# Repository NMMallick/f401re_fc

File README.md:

# f401re_fc
Amateur prototype for a quad-copter flightcontroller on stm32f4 based chips

##

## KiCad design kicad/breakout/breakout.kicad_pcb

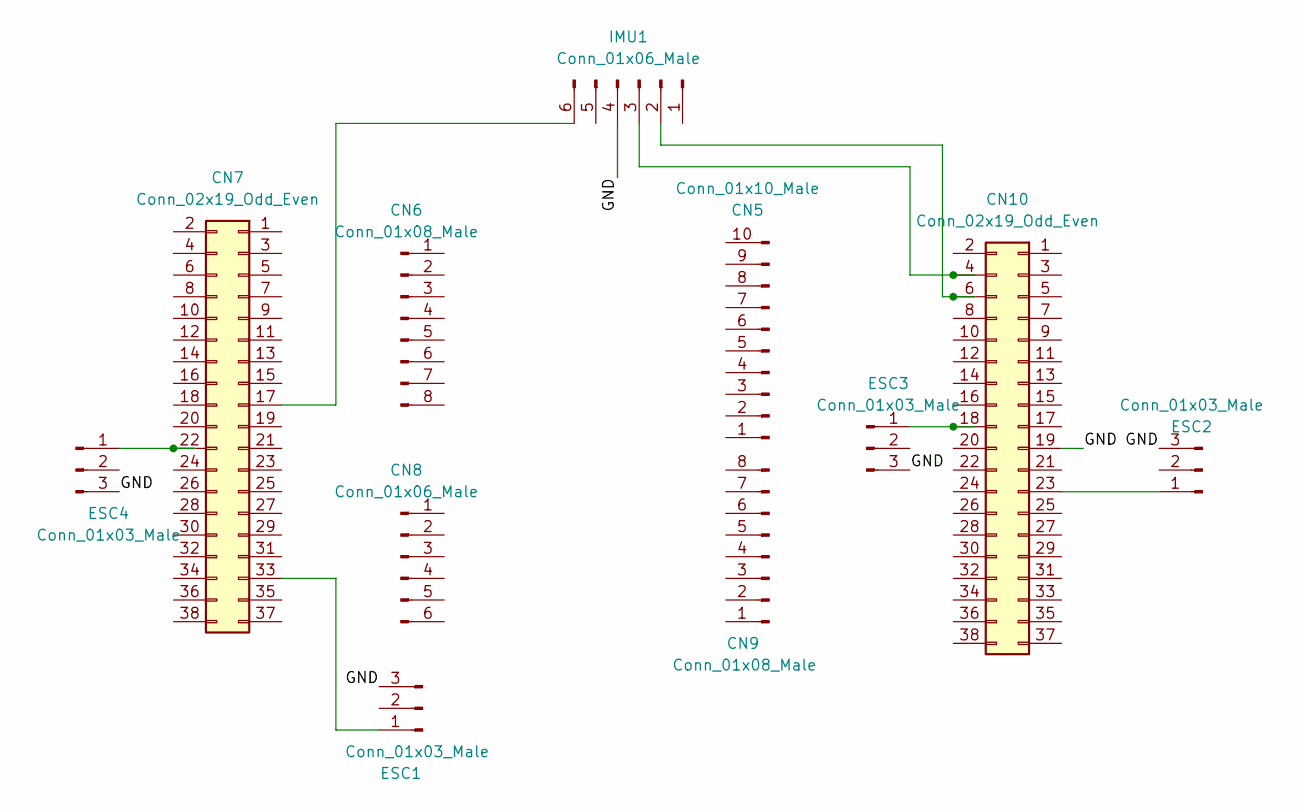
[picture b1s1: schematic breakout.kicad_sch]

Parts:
CN5: Conn_01x10_Male; PinHeader_1x10_P2.54mm_Vertical
CN6, CN9: Conn_01x08_Male; PinHeader_1x08_P2.54mm_Vertical
CN7, CN10: Conn_02x19_Odd_Even; PinSocket_2x19_P2.54mm_Vertical
CN8: Conn_01x06_Male; PinHeader_1x06_P2.54mm_Vertical
ESC1, ESC2, ESC3, ESC4: Conn_01x03_Male; PinHeader_1x03_P2.54mm_Vertical
IMU1: Conn_01x06_Male; PinHeader_1x06_P2.54mm_Vertical

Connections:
/GND: CN10.19, ESC1.3, ESC2.3, ESC3.3, ESC4.3, IMU1.4
unnamed: CN7.22, ESC4.1
unnamed: CN10.23, ESC2.1
unnamed: CN7.33, ESC1.1
unnamed: CN10.18, ESC3.1
unnamed: CN10.6, IMU1.2
unnamed: CN10.4, IMU1.3
unnamed: CN7.17, IMU1.6

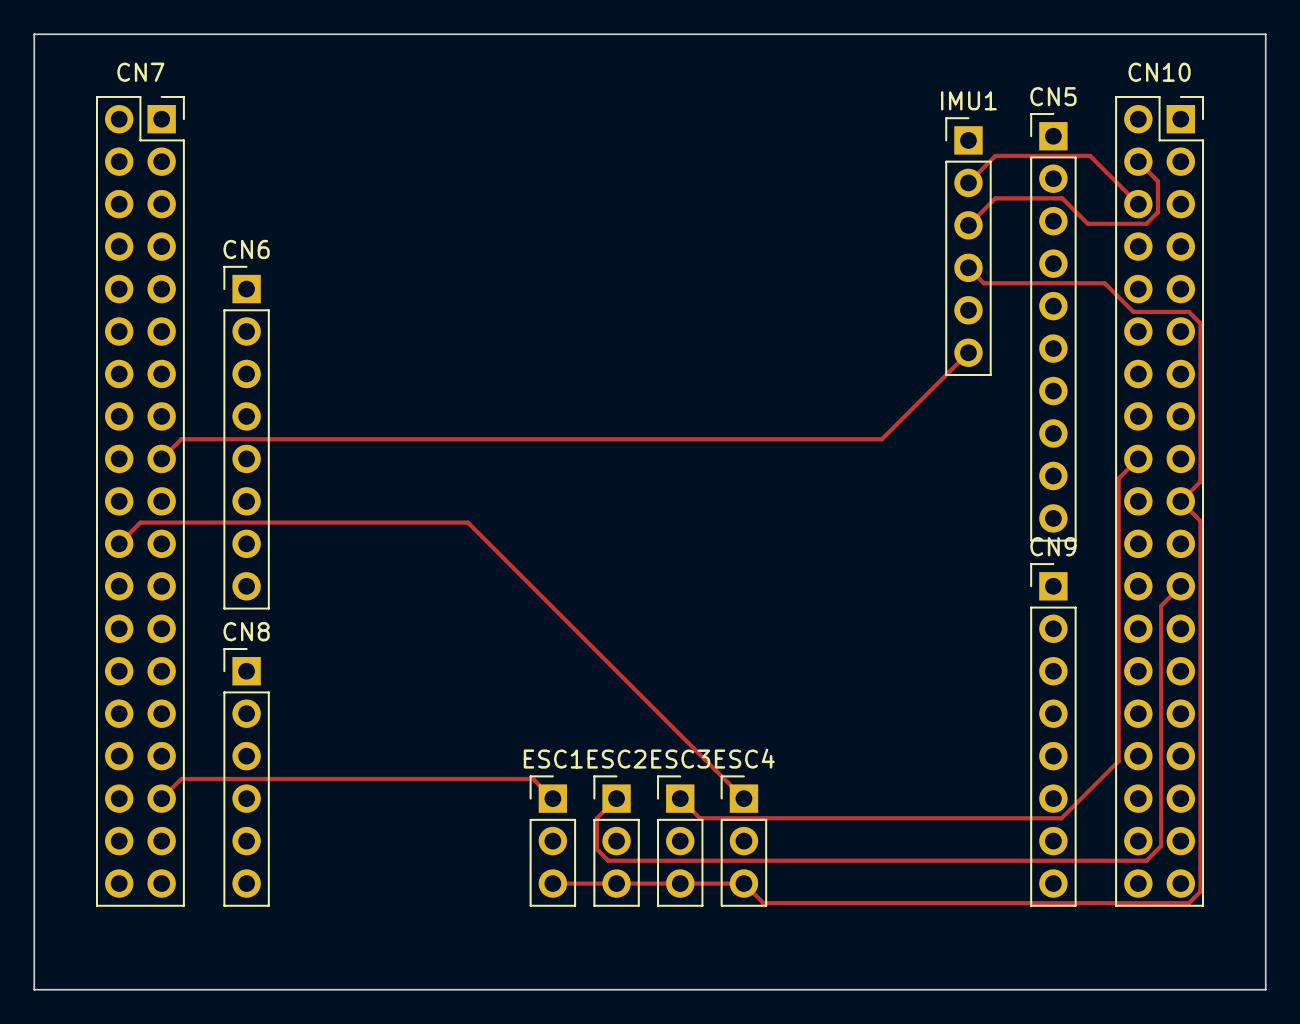
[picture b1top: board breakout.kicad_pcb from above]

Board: 2 copper layers, 73.7 x 57.1 mm, 11 parts (0 on the bottom side), 8 nets.

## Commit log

2023-01-13 initializing repository
2023-01-14 removing random file
2023-01-14 added flash action to Makefile
2023-01-15 eg. for DMA->PWM access
2023-01-17 added pwm and dma config
2023-01-17 removed comments
2023-01-17 testing pwm signal
2023-01-17 hoping the pwm, dma works
2023-01-18 packet structure for dshot frame
2023-01-18 initial test for dshot impl
2023-01-18 preliminary dshot protocol testing
2023-01-24 creating seperate library for the dshot impl
2023-01-24 fixing dshot library
2023-01-25 re-generate main.c
2023-01-25 adding all 4 motor channels
2023-01-25 debugging
2023-01-25 debugging dshot lib
2023-01-25 updating remote
2023-01-25 adding callback to hal tim
2023-01-25 changing tim pins for pwm generation
2023-01-26 refactoring how timers are stored
2023-01-26 refactoring to use structs
2023-01-26 testing gpg key
2023-02-01 finalized pwm timers for each motor
2023-02-02 added comments to header functions
2023-02-15 Testing implementation of uart with DMA
2023-02-15 removed commented sections
2023-02-22 testing 4 channels comms via uart
2023-02-23 testing uart integrity w/ dma
2023-02-24 figuring out flashing tool issues
2023-02-25 setting PWM dma priority to high
2023-02-25 branch integration testing(offboard)
2023-02-27 tested motor mixer algo
2023-06-17 adding kicad files for nucleo breakout board
2023-06-17 updated .gitignore to ignore kicad output files
2023-09-10 updated global variables to be static, adding ekf impl, updating .gitignore
2023-09-19 adding cmatrix submodule
